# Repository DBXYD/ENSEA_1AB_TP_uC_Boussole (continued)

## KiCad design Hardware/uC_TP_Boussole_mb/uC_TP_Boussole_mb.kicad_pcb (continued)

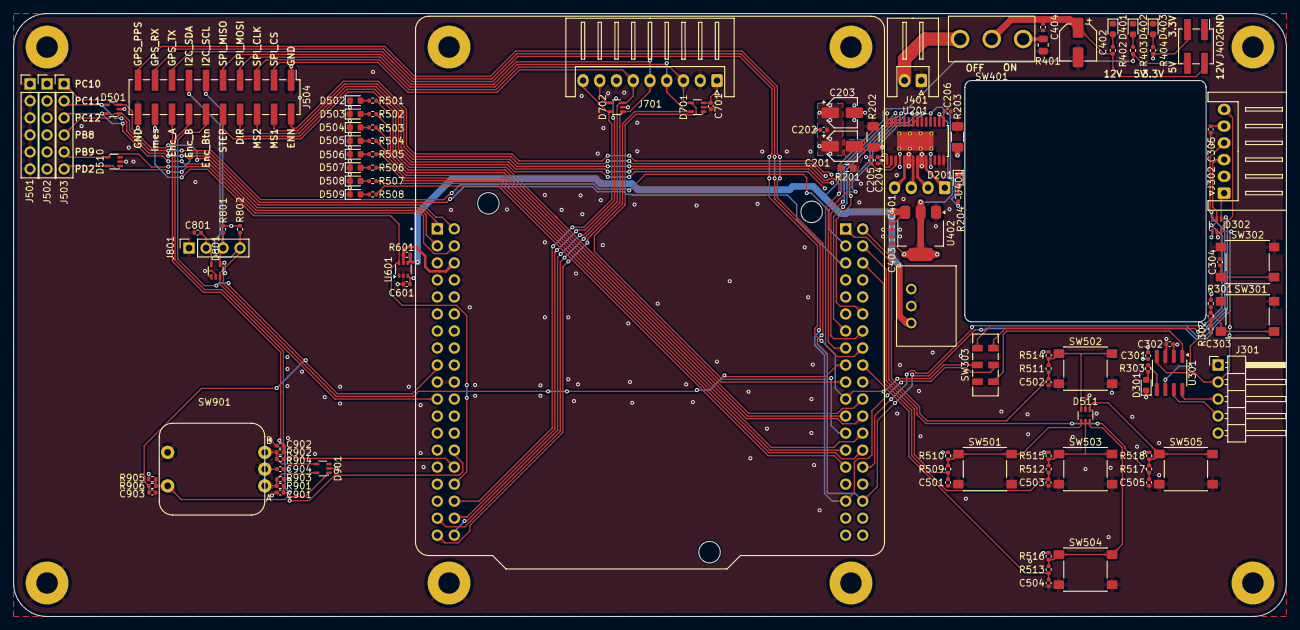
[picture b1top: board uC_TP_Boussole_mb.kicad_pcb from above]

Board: 4 copper layers, 190.0 x 90.0 mm, 121 parts (1 on the bottom side), 89 nets.

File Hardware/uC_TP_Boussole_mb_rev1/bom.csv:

Reference,Value,Footprint,Qty,MPN
C303,10n,Capacitor_SMD:C_0402_1005Metric,1,WE 885012205050
C501,10n,Capacitor_SMD:C_0402_1005Metric,1,WE 885012205050
C502,10n,Capacitor_SMD:C_0402_1005Metric,1,WE 885012205050
C503,10n,Capacitor_SMD:C_0402_1005Metric,1,WE 885012205050
C504,10n,Capacitor_SMD:C_0402_1005Metric,1,WE 885012205050
C505,10n,Capacitor_SMD:C_0402_1005Metric,1,WE 885012205050
C901,10n,Capacitor_SMD:C_0402_1005Metric,1,WE 885012205050
C902,10n,Capacitor_SMD:C_0402_1005Metric,1,WE 885012205050
C903,10n,Capacitor_SMD:C_0402_1005Metric,1,WE 885012205050
C204,22n,Capacitor_SMD:C_0402_1005Metric,1,WE 885012205052
C202,100n,Capacitor_SMD:C_0402_1005Metric,1,WE 885012105018
C205,100n,Capacitor_SMD:C_0402_1005Metric,1,WE 885012105018
C302,100n,Capacitor_SMD:C_0402_1005Metric,1,WE 885012105018
C304,100n,Capacitor_SMD:C_0402_1005Metric,1,WE 885012105018
C404,100n,Capacitor_SMD:C_0402_1005Metric,1,WE 885012105018
C601,100n,Capacitor_SMD:C_0402_1005Metric,1,WE 885012105018
C904,100n,Capacitor_SMD:C_0402_1005Metric,1,WE 885012105018
C305,1u,Capacitor_SMD:C_0402_1005Metric,1,WE 885012105012
C701,1u,Capacitor_SMD:C_0402_1005Metric,1,WE 885012105012
C801,1u,Capacitor_SMD:C_0402_1005Metric,1,WE 885012105012
C201,10u,Capacitor_SMD:CP_Elec_4x5.7,1,WE 865060440001
C203,10u,Capacitor_SMD:CP_Elec_4x5.7,1,WE 865060440001
C401,10u,Capacitor_SMD:C_0402_1005Metric,1,WE  885012105020
C403,10u,Capacitor_SMD:C_0402_1005Metric,1,WE  885012105020
C402,22u,Capacitor_SMD:CP_Elec_5x5.4,1,WE 865060442002
R601,400m,Resistor_SMD:R_0402_1005Metric,1,WW04PR400FTL
R201,110m,Resistor_SMD:R_0603_1608Metric_Pad0.98x0.95mm_HandSolder,1,MFL0603R1100FB 
R202,680m,Resistor_SMD:R_1206_3216Metric_Pad1.30x1.75mm_HandSolder,1,WW12PR680FTL 
R203,680m,Resistor_SMD:R_1206_3216Metric_Pad1.30x1.75mm_HandSolder,1,WW12PR680FTL 
R504,400,Resistor_SMD:R_0402_1005Metric,1,
R505,400,Resistor_SMD:R_0402_1005Metric,1,
R506,400,Resistor_SMD:R_0402_1005Metric,1,
R507,400,Resistor_SMD:R_0402_1005Metric,1,
R508,400,Resistor_SMD:R_0402_1005Metric,1,
R303,800,Resistor_SMD:R_0402_1005Metric,1,
R501,800,Resistor_SMD:R_0402_1005Metric,1,
R503,800,Resistor_SMD:R_0402_1005Metric,1,
R204,820,Resistor_SMD:R_0402_1005Metric,1,
R404,820,Resistor_SMD:R_0402_1005Metric,1,
R502,850,Resistor_SMD:R_0402_1005Metric,1,
R401,1k,Resistor_SMD:R_0805_2012Metric,1,
R801,1k,Resistor_SMD:R_0402_1005Metric,1,
R802,1k,Resistor_SMD:R_0402_1005Metric,1,
R301,10k,Resistor_SMD:R_0402_1005Metric,1,
R302,10k,Resistor_SMD:R_0402_1005Metric,1,
R509,10k,Resistor_SMD:R_0402_1005Metric,1,
R510,10k,Resistor_SMD:R_0402_1005Metric,1,
R511,10k,Resistor_SMD:R_0402_1005Metric,1,
R512,10k,Resistor_SMD:R_0402_1005Metric,1,
R513,10k,Resistor_SMD:R_0402_1005Metric,1,
R514,10k,Resistor_SMD:R_0402_1005Metric,1,
R515,10k,Resistor_SMD:R_0402_1005Metric,1,
R516,10k,Resistor_SMD:R_0402_1005Metric,1,
R517,10k,Resistor_SMD:R_0402_1005Metric,1,
R518,10k,Resistor_SMD:R_0402_1005Metric,1,
R901,10k,Resistor_SMD:R_0402_1005Metric,1,
R902,10k,Resistor_SMD:R_0402_1005Metric,1,
R903,10k,Resistor_SMD:R_0402_1005Metric,1,
R904,10k,Resistor_SMD:R_0402_1005Metric,1,
R905,10k,Resistor_SMD:R_0402_1005Metric,1,
R906,10k,Resistor_SMD:R_0402_1005Metric,1,
U401,173010542,libs:173010xxx,1,WE 173010542
R403,1k6,Resistor_SMD:R_0402_1005Metric,1,
C206,4u7,Capacitor_SMD:C_0402_1005Metric,1,WE 885012105008
C301,4u7,Capacitor_SMD:C_0402_1005Metric,1,WE 885012105008
R402,5k1,Resistor_SMD:R_0402_1005Metric,1,
D503,AMBER_LED,LED_SMD:LED_0603_1608Metric,1,WE 150060AS55040
U402,AZ1117CH2-3.3TRG1,Package_TO_SOT_SMD:SOT-223-3_TabPin2,1,AZ1117CH2-3.3TRG1
J401,Conn_01x02,Connector_JST:JST_XH_S2B-XH-A_1x02_P2.50mm_Horizontal,1,S2B-XH-A(lf)(sn)
J201,Conn_01x04,Connector_JST:JST_XH_S4B-XH-A_1x04_P2.50mm_Horizontal,1,S4B-XH-A(lf)(sn)
J801,Conn_01x04,libs:SBC-OLED01,1,Joy-it SBC-OLED01
J301,Conn_01x05,Connector_PinHeader_2.54mm:PinHeader_1x05_P2.54mm_Horizontal,1,
J302,Conn_01x06,Connector_JST:JST_XH_S6B-XH-A_1x06_P2.50mm_Horizontal,1,S6B-XH-A(lf)(sn)
J501,Conn_01x06,Connector_PinHeader_2.54mm:PinHeader_1x06_P2.54mm_Vertical,1,SAMTEC TSW-106-05-F-T 
J502,Conn_01x06,Connector_PinHeader_2.54mm:PinHeader_1x06_P2.54mm_Vertical,1,SAMTEC TSW-106-05-F-T 
J503,Conn_01x06,Connector_PinHeader_2.54mm:PinHeader_1x06_P2.54mm_Vertical,1,SAMTEC TSW-106-05-F-T 
J701,Conn_01x09,Connector_JST:JST_XH_S9B-XH-A_1x09_P2.50mm_Horizontal,1,S9B-XH-A (LF)(SN)
J402,Conn_02x02_Counter_Clockwise,Connector_PinHeader_2.54mm:PinHeader_2x02_P2.54mm_Vertical_SMD,1,WE 61000421121
J504,Conn_02x10_Odd_Even,Connector_PinHeader_2.54mm:PinHeader_2x10_P2.54mm_Vertical_SMD,1,WE 61002021121
D505,GREEN_LED,LED_SMD:LED_0603_1608Metric,1,WE 150060GS55040
D506,GREEN_LED,LED_SMD:LED_0603_1608Metric,1,WE 150060GS55040
D507,GREEN_LED,LED_SMD:LED_0603_1608Metric,1,WE 150060GS55040
D508,GREEN_LED,LED_SMD:LED_0603_1608Metric,1,WE 150060GS55040
D509,GREEN_LED,LED_SMD:LED_0603_1608Metric,1,WE 150060GS55040
H101,MountingHole_Pad,MountingHole:MountingHole_3.2mm_M3_Pad,1,
H102,MountingHole_Pad,MountingHole:MountingHole_3.2mm_M3_Pad,1,
H103,MountingHole_Pad,MountingHole:MountingHole_3.2mm_M3_Pad,1,
H104,MountingHole_Pad,MountingHole:MountingHole_3.2mm_M3_Pad,1,
H105,MountingHole_Pad,MountingHole:MountingHole_3.2mm_M3_Pad,1,
H106,MountingHole_Pad,MountingHole:MountingHole_3.2mm_M3_Pad,1,
H107,MountingHole_Pad,MountingHole:MountingHole_3.2mm_M3_Pad,1,
H108,MountingHole_Pad,MountingHole:MountingHole_3.2mm_M3_Pad,1,
U601,NCS199A3RSQT2G,Package_TO_SOT_SMD:SOT-363_SC-70-6,1,NCS199A3RSQT2G
U501,NUCLEO_L476RG,libs:ST_NUCLEO_64,1,TSW-119-19-T-D 
D201,RED_LED,LED_SMD:LED_0603_1608Metric,1,WE 150060RS55040
D301,RED_LED,LED_SMD:LED_0603_1608Metric,1,WE 150060RS55040
D401,RED_LED,LED_SMD:LED_0603_1608Metric,1,WE 150060RS55040
D402,RED_LED,LED_SMD:LED_0603_1608Metric,1,WE 150060RS55040
D403,RED_LED,LED_SMD:LED_0603_1608Metric,1,WE 150060RS55040
D502,RED_LED,LED_SMD:LED_0603_1608Metric,1,WE 150060RS55040
SW901,RotaryEncoder_Switch,libs:482016514001_Mechanical_Incremental_Encoder_Switch,1,WE 482016514001
U301,STM32C011J4Mx,Package_SO:SOIC-8_3.9x4.9mm_P1.27mm,1,STM32C011J4M6
SW301,SW_Push,Button_Switch_SMD:SW_Push_1P1T_NO_6x6mm_H9.5mm,1,WE 430182070816
SW302,SW_Push,Button_Switch_SMD:SW_Push_1P1T_NO_6x6mm_H9.5mm,1,WE 430182070816
SW501,SW_Push,Button_Switch_SMD:SW_Push_1P1T_NO_6x6mm_H9.5mm,1,WE 430182070816
SW502,SW_Push,Button_Switch_SMD:SW_Push_1P1T_NO_6x6mm_H9.5mm,1,WE 430182070816
SW503,SW_Push,Button_Switch_SMD:SW_Push_1P1T_NO_6x6mm_H9.5mm,1,WE 430182070816
SW504,SW_Push,Button_Switch_SMD:SW_Push_1P1T_NO_6x6mm_H9.5mm,1,WE 430182070816
SW505,SW_Push,Button_Switch_SMD:SW_Push_1P1T_NO_6x6mm_H9.5mm,1,WE 430182070816
SW303,SW_Push_DPDT,Button_Switch_SMD:SW_DPDT_CK_JS202011JCQN,1,JS202011JCQN
SW401,SW_SPDT,libs:472121020311,1,WE 472121020311
U201,TMC2225-SA-T,Package_SO:HTSSOP-28-1EP_4.4x9.7mm_P0.65mm_EP2.85x5.4mm_ThermalVias,1,TMC2225-SA-T
D501,WE 82402374,libs:SC70-5L,1,WE 82402374
D510,WE 82402374,libs:SC70-5L,1,WE 82402374
D701,WE 82402374,libs:SC70-5L,1,WE 82402374
D702,WE 82402374,libs:SC70-5L,1,WE 82402374
D801,WE 82402374,libs:SC70-5L,1,WE 82402374
D901,WE 82402374,libs:SC70-5L,1,WE 82402374
D302,WE 82402375,libs:SC70-6L,1,WE 82402375
D511,WE 82402375,libs:SC70-6L,1,WE 82402375
D504,YELLOW_LED,LED_SMD:LED_0603_1608Metric,1,WE 150060YS55040

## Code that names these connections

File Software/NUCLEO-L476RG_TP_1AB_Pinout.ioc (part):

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Mcu.Name=STM32L476R(C-E-G)Tx
Mcu.Package=LQFP64
Mcu.UserName=STM32L476RGTx
PA0.Signal=S_TIM2_CH1
PA1.Signal=S_TIM2_CH2
PA10.Mode=Asynchronous
PA10.Signal=USART1_RX
PA11.GPIOParameters=GPIO_Label
PA11.GPIO_Label=STEPPER_MS1
PA11.Signal=GPIO_Output
PA12.GPIOParameters=GPIO_Label
PA12.GPIO_Label=STEPPER_ENN
PA12.Signal=GPIO_Output
PA13\ (JTMS-SWDIO).GPIOParameters=GPIO_Label
PA13\ (JTMS-SWDIO).GPIO_Label=TMS
PA13\ (JTMS-SWDIO).Mode=Trace_Asynchronous_SW
PA13\ (JTMS-SWDIO).Signal=SYS_JTMS-SWDIO
PA14\ (JTCK-SWCLK).GPIOParameters=GPIO_Label
PA14\ (JTCK-SWCLK).GPIO_Label=TCK
PA14\ (JTCK-SWCLK).Mode=Trace_Asynchronous_SW
PA14\ (JTCK-SWCLK).Signal=SYS_JTCK-SWCLK
PA15\ (JTDI).GPIOParameters=GPIO_Label
PA15\ (JTDI).GPIO_Label=ENC_BTN
PA15\ (JTDI).Signal=GPXTI15
PA2.GPIOParameters=GPIO_Speed,GPIO_PuPd,GPIO_Label,GPIO_Mode
PA2.GPIO_Label=USART_TX
PA2.GPIO_Mode=GPIO_MODE_AF_PP
PA2.GPIO_PuPd=GPIO_NOPULL
PA2.GPIO_Speed=GPIO_SPEED_FREQ_VERY_HIGH
PA2.Mode=Asynchronous
PA2.Signal=USART2_TX
PA3.GPIOParameters=GPIO_Speed,GPIO_PuPd,GPIO_Label,GPIO_Mode
PA3.GPIO_Label=USART_RX
PA3.GPIO_Mode=GPIO_MODE_AF_PP
PA3.GPIO_PuPd=GPIO_NOPULL
PA3.GPIO_Speed=GPIO_SPEED_FREQ_VERY_HIGH
PA3.Mode=Asynchronous
PA3.Signal=USART2_RX
PA4.Signal=ADCx_IN9
PA5.GPIOParameters=GPIO_Speed,GPIO_PuPd,GPIO_Label,GPIO_ModeDefaultOutputPP
PA5.GPIO_Label=LD2 [green Led]
PA5.GPIO_ModeDefaultOutputPP=GPIO_MODE_OUTPUT_PP
PA5.GPIO_PuPd=GPIO_NOPULL
PA5.GPIO_Speed=GPIO_SPEED_FREQ_LOW
PA5.Signal=GPIO_Output
PA6.Signal=S_TIM3_CH1
PA7.GPIOParameters=GPIO_Label
PA7.GPIO_Label=STEPPER_DIR
PA7.Signal=GPIO_Output
PA8.GPIOParameters=GPIO_Label
PA8.GPIO_Label=LED_2
PA8.Signal=GPIO_Output
PA9.Mode=Asynchronous
PA9.Signal=USART1_TX
PB0.GPIOParameters=GPIO_Label
PB0.GPIO_Label=MAGNETO_INT
PB0.Signal=GPXTI0
PB1.GPIOParameters=GPIO_Label
PB1.GPIO_Label=LED_3
PB1.Signal=GPIO_Output
PB10.Mode=Full_Duplex_Master
PB10.Signal=SPI2_SCK
PB11.GPIOParameters=GPIO_Label
PB11.GPIO_Label=BTN_TOP
PB11.Signal=GPXTI11
PB13.GPIOParameters=GPIO_Label
PB13.GPIO_Label=GPS_ENN
PB13.Signal=GPIO_Output
PB14.GPIOParameters=GPIO_Label
PB14.GPIO_Label=LED_6
PB14.Signal=GPIO_Output
PB15.GPIOParameters=GPIO_Label
PB15.GPIO_Label=LED_4
PB15.Signal=GPIO_Output
PB2.GPIOParameters=GPIO_Label
PB2.GPIO_Label=LED_1
PB2.Signal=GPIO_Output
PB3\ (JTDO-TRACESWO).Mode=Trace_Asynchronous_SW
PB3\ (JTDO-TRACESWO).Signal=SYS_JTDO-SWO
PB4\ (NJTRST).GPIOParameters=GPIO_Label
PB4\ (NJTRST).GPIO_Label=LED_5
PB4\ (NJTRST).Signal=GPIO_Output
PB5.GPIOParameters=GPIO_Label
PB5.GPIO_Label=LED_7
PB5.Signal=GPIO_Output
PB6.Mode=I2C
PB6.Signal=I2C1_SCL
PB7.Mode=I2C
PB7.Signal=I2C1_SDA
PC0.GPIOParameters=GPIO_Label
PC0.GPIO_Label=SPI_CS
PC0.Signal=GPIO_Output
PC1.GPIOParameters=GPIO_Label
PC1.GPIO_Label=MAGNETO_STATUS
PC1.Signal=GPIO_Input
PC10.GPIOParameters=GPIO_Label
PC10.GPIO_Label=PC10
PC10.Signal=GPIO_Output
PC13.GPIOParameters=GPIO_PuPd,GPIO_Label,GPIO_ModeDefaultEXTI
PC13.GPIO_Label=B1 [Blue PushButton]
PC13.GPIO_ModeDefaultEXTI=GPIO_MODE_IT_FALLING
PC13.GPIO_PuPd=GPIO_NOPULL
PC13.Signal=GPXTI13
PC14-OSC32_IN\ (PC14).Mode=LSE-External-Oscillator
PC14-OSC32_IN\ (PC14).Signal=RCC_OSC32_IN
PC15-OSC32_OUT\ (PC15).Mode=LSE-External-Oscillator
PC15-OSC32_OUT\ (PC15).Signal=RCC_OSC32_OUT
PC2.Mode=Full_Duplex_Master
PC2.Signal=SPI2_MISO
PC3.Mode=Full_Duplex_Master
PC3.Signal=SPI2_MOSI
PC4.GPIOParameters=GPIO_Label
PC4.GPIO_Label=GPS_PPS
PC4.Signal=GPXTI4
PC5.GPIOParameters=GPIO_Label
PC5.GPIO_Label=BTN_TOP
PC5.Signal=GPXTI5
PC6.GPIOParameters=GPIO_Label
PC6.GPIO_Label=BTN_CENTER
PC6.Signal=GPXTI6
PC7.GPIOParameters=GPIO_Label
PC7.GPIO_Label=LED_0
PC7.Signal=GPIO_Output
PC8.GPIOParameters=GPIO_Label
PC8.GPIO_Label=BTN_RIGHT
PC8.Signal=GPXTI8
PC9.GPIOParameters=GPIO_Label
PC9.GPIO_Label=BTN_LEFT
PC9.Signal=GPXTI9
PH0-OSC_IN\ (PH0).Mode=HSE-External-Oscillator
PH0-OSC_IN\ (PH0).Signal=RCC_OSC_IN
PH1-OSC_OUT\ (PH1).Mode=HSE-External-Oscillator
PH1-OSC_OUT\ (PH1).Signal=RCC_OSC_OUT
RCC.HSE_VALUE=8000000
RCC.SYSCLKFreq_VALUE=80000000
RCC.SYSCLKSource=RCC_SYSCLKSOURCE_PLLCLK
board=NUCLEO-L476RG
boardIOC=true

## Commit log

2024-03-03 update schematic
2024-03-04 starting pin out nucleo
2024-03-05 update pcb
2024-03-06 update ppcb
2024-03-20 finalize pcb
2024-03-21 change SBC01 footprint, add via GND, clean error and export gerbers
2024-03-24 create BOM, update MPN
2024-07-17 create rev 2 pcb
2024-09-06 export files for production
